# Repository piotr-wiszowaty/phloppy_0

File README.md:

phloppy\_0
=========

phloppy\_0 is a [Commodore Amiga](https://en.wikipedia.org/wiki/Amiga) floppy
drive emulator. It emulates four drives (`DF0:`, `DF1:`, `DF2:`, `DF3:`) and
is controlled through WiFi by an Android or a PC application.

`DF0:` - `DF3:` interoperation
--------------------------

The device is connected between the Amiga motherboard and the internal floppy
drive (DF0:). When a floppy image is inserted in the virtual DF0: the physical
drive input signals `SEL0` and `MTR0` are inactive. When there is no floppy image
in the virtual DF0: the `SEL0` and `MTR0` signals are passed from the Amiga
motherboard through the emulator to the physical drive.

When there are `DF1:` - `DF3`: physical drives connected to the Amiga, inserting
a floppy image in any of the virtual `DF1:` - `DF3:` will result in malfunction
of the drive.

Supported floppy image formats
------------------------------
 
Two floppy image formats are supported:
- ADF ([Amiga Disk File](https://en.wikipedia.org/wiki/Amiga\_Disk\_File)), 880 kB
- raw MFM - 12668 bytes per track, 160 tracks per disk

Hardware
--------

Main hardware components:
- STM32F446 - Cortex-M4 microcontroller; core of the emulator
- SDRAM, 8 MB; used for keeping floppy image contents
- ESP12-E - ESP8266 based WiFi module; provides WiFi hotspot to allow connection
  of a controlling application
- XC9272XL CPLD & two 8-channel open-drain buffers - interface between the
  microcontroller and the Amiga motherboard

On-board connectors:
- micro USB - for flashing the microcontroller
- SWD - for flashing/debugging the microcontroller
- JTAG - for flashing the CPLD
- UART (3.3 V) - for flashing the ESP8266
- power input - from the Amiga motherboard
- power output - to the physical floppy drive
- SEL2, SEL3 - input for the appropriate floppy selection signals
- male 34-pin pinheader - for connecting through a ribbon cable with
  the Amiga motherboard; for A600 the cable should be around 155 mm long
- female 34-pin pinheader - for connecting directly to the physical floppy
  drive

LEDs:
- green - indicates SDRAM active
- yellow - indicates read operation in progress
- red - indicates communication with the controlling application
  in progress
- blue - indicates write buffer is not empty (turn on the controlling
  application to write the buffer to the persistent memory)

In idle mode the device consumes around 170 mA. When the SDRAM is in active
mode the current consumption is around 185 mA.

Software
--------

Software components:
- `android/` - Android control application sources
- `cpld/` - CPLD design files
- `output/` - APK, JED, Gerbers, microcontroller firmware
- `pc/` - PC control application sources
- `uc/` - microcontroller firmware sources
- `wifi/` - ESP8266 source files

The Android application requires SDK level 15 and works at least on
Android 4.0.3 and 8.0.0.

The WiFi hotspot parameters are stored in the STM32 microcontroller and
read by ESP8266 during initialization. The parameters can be changed in source
code or after compilation in the microcontroller firmware image file.

License
-------

The project is licensed under GPL-3.0 license. See `LICENSE` for more information.
Parts of the project are covered by other licenses (see appropriate files for details):
- ESP8266 SPI driver by David Ogilvy (MetalPhreak)
- CMSIS header files by ARM LIMITED
- STM32 header files by STMicroelectronics

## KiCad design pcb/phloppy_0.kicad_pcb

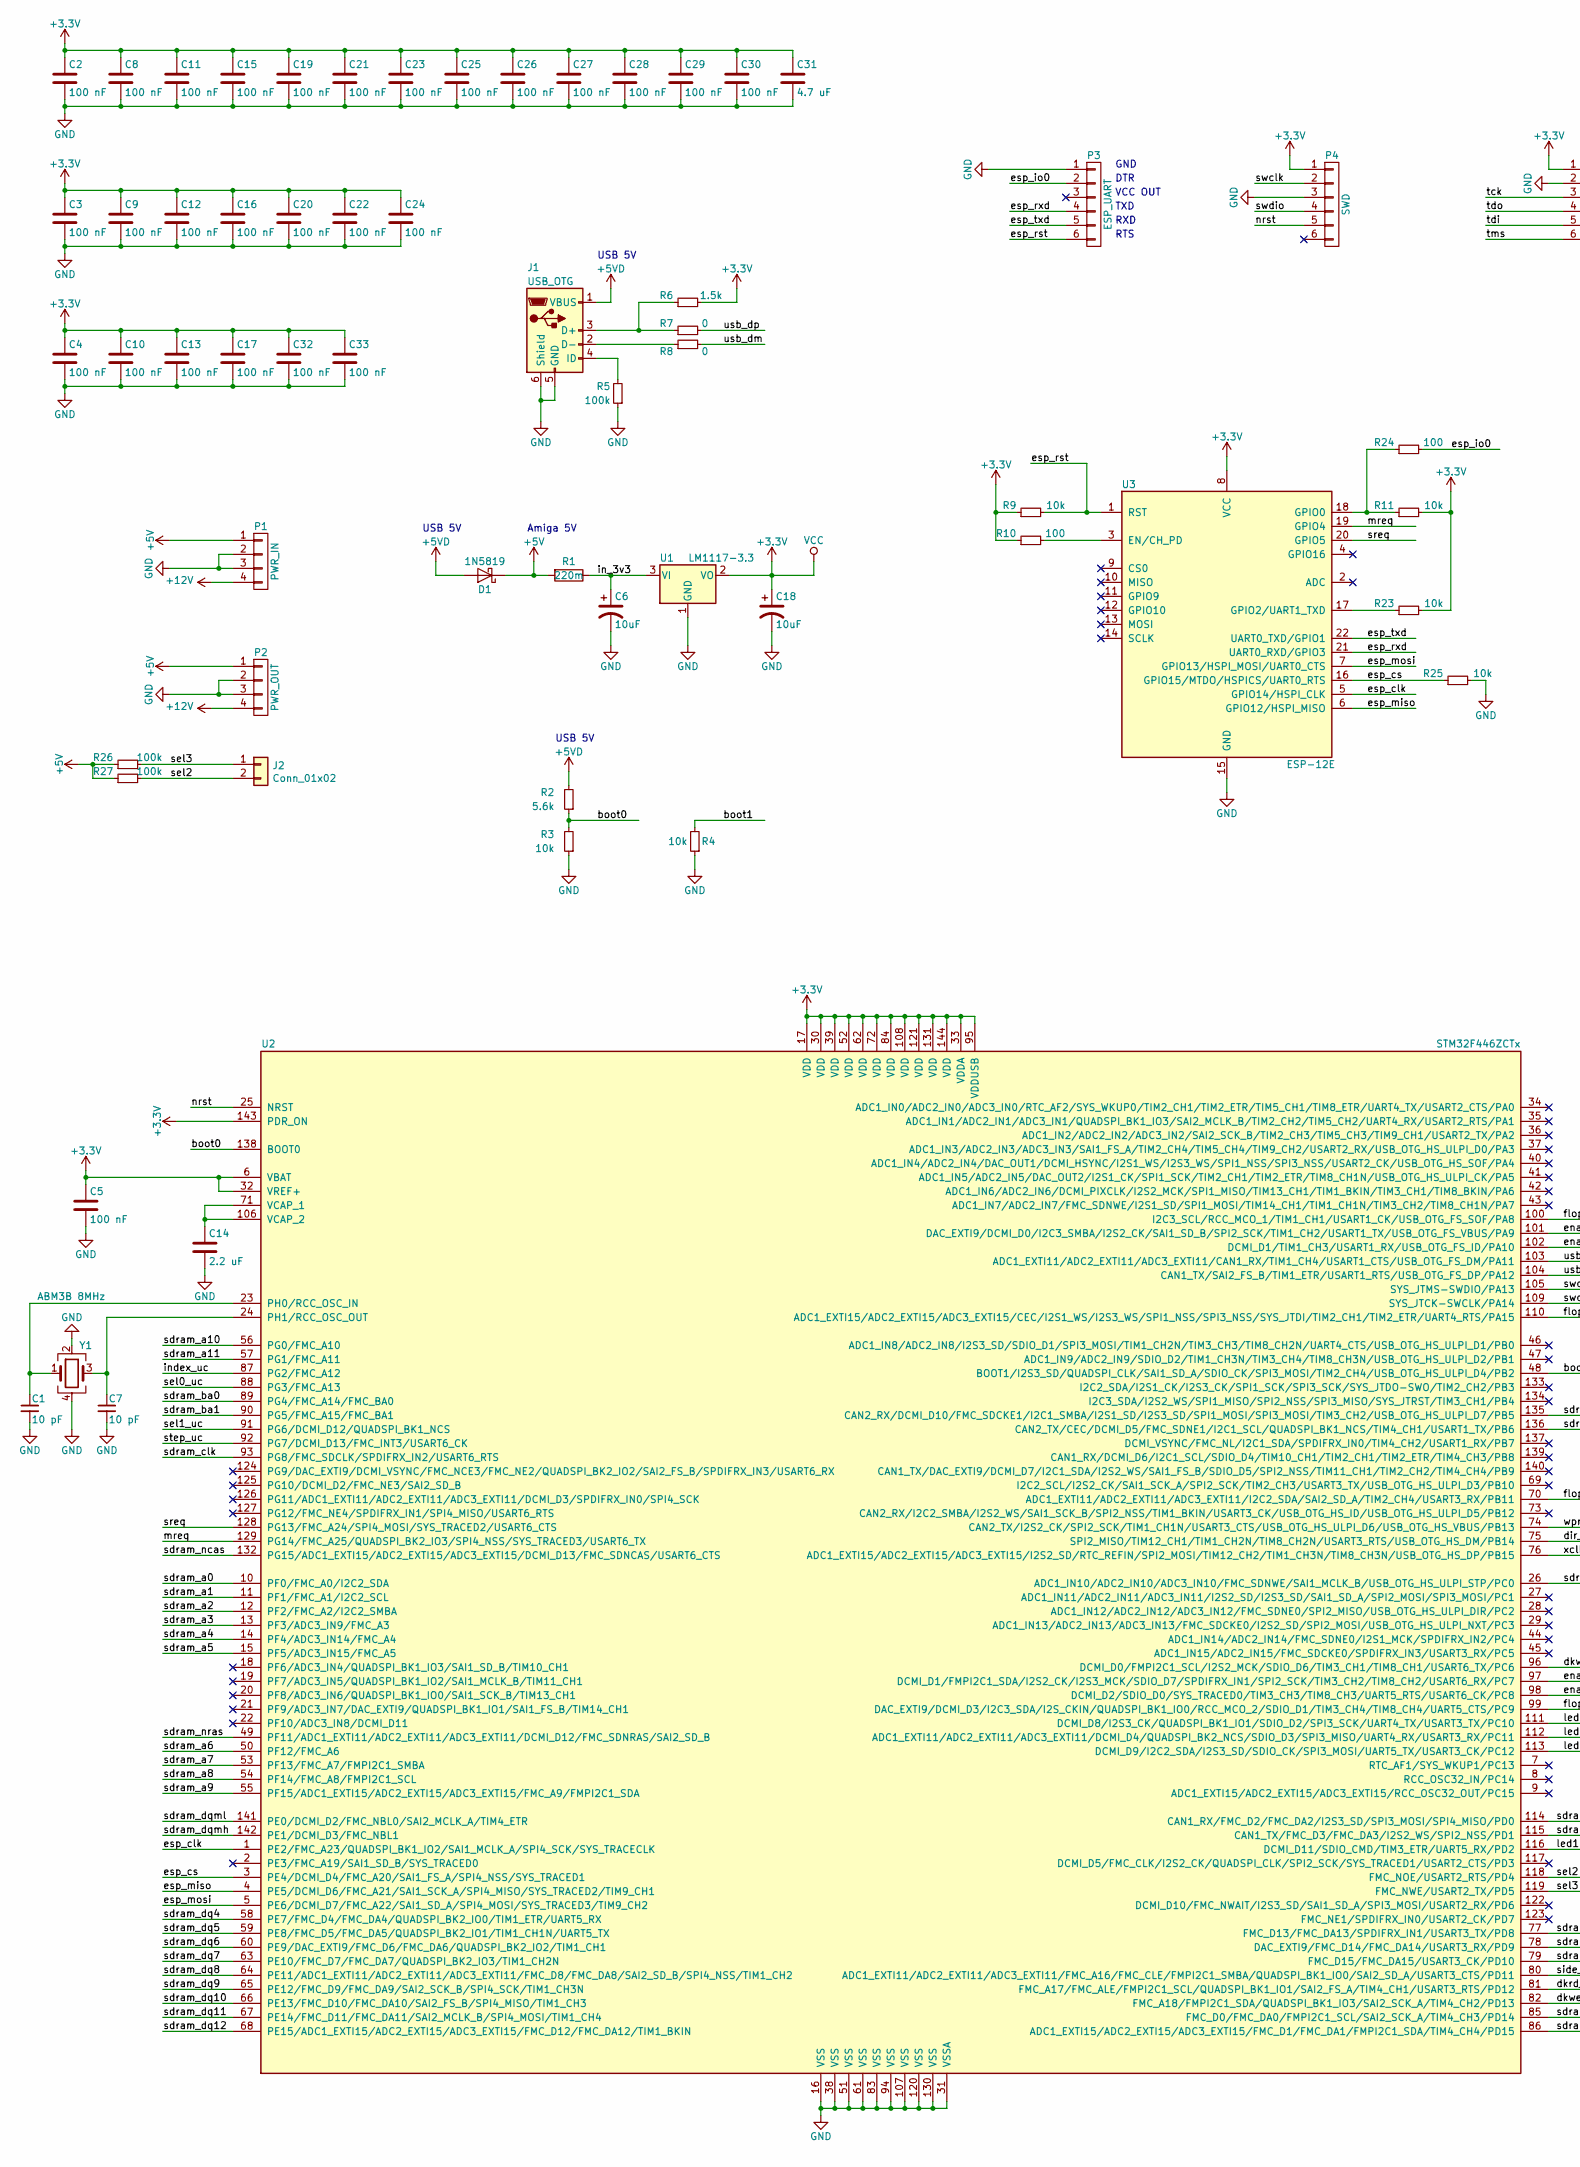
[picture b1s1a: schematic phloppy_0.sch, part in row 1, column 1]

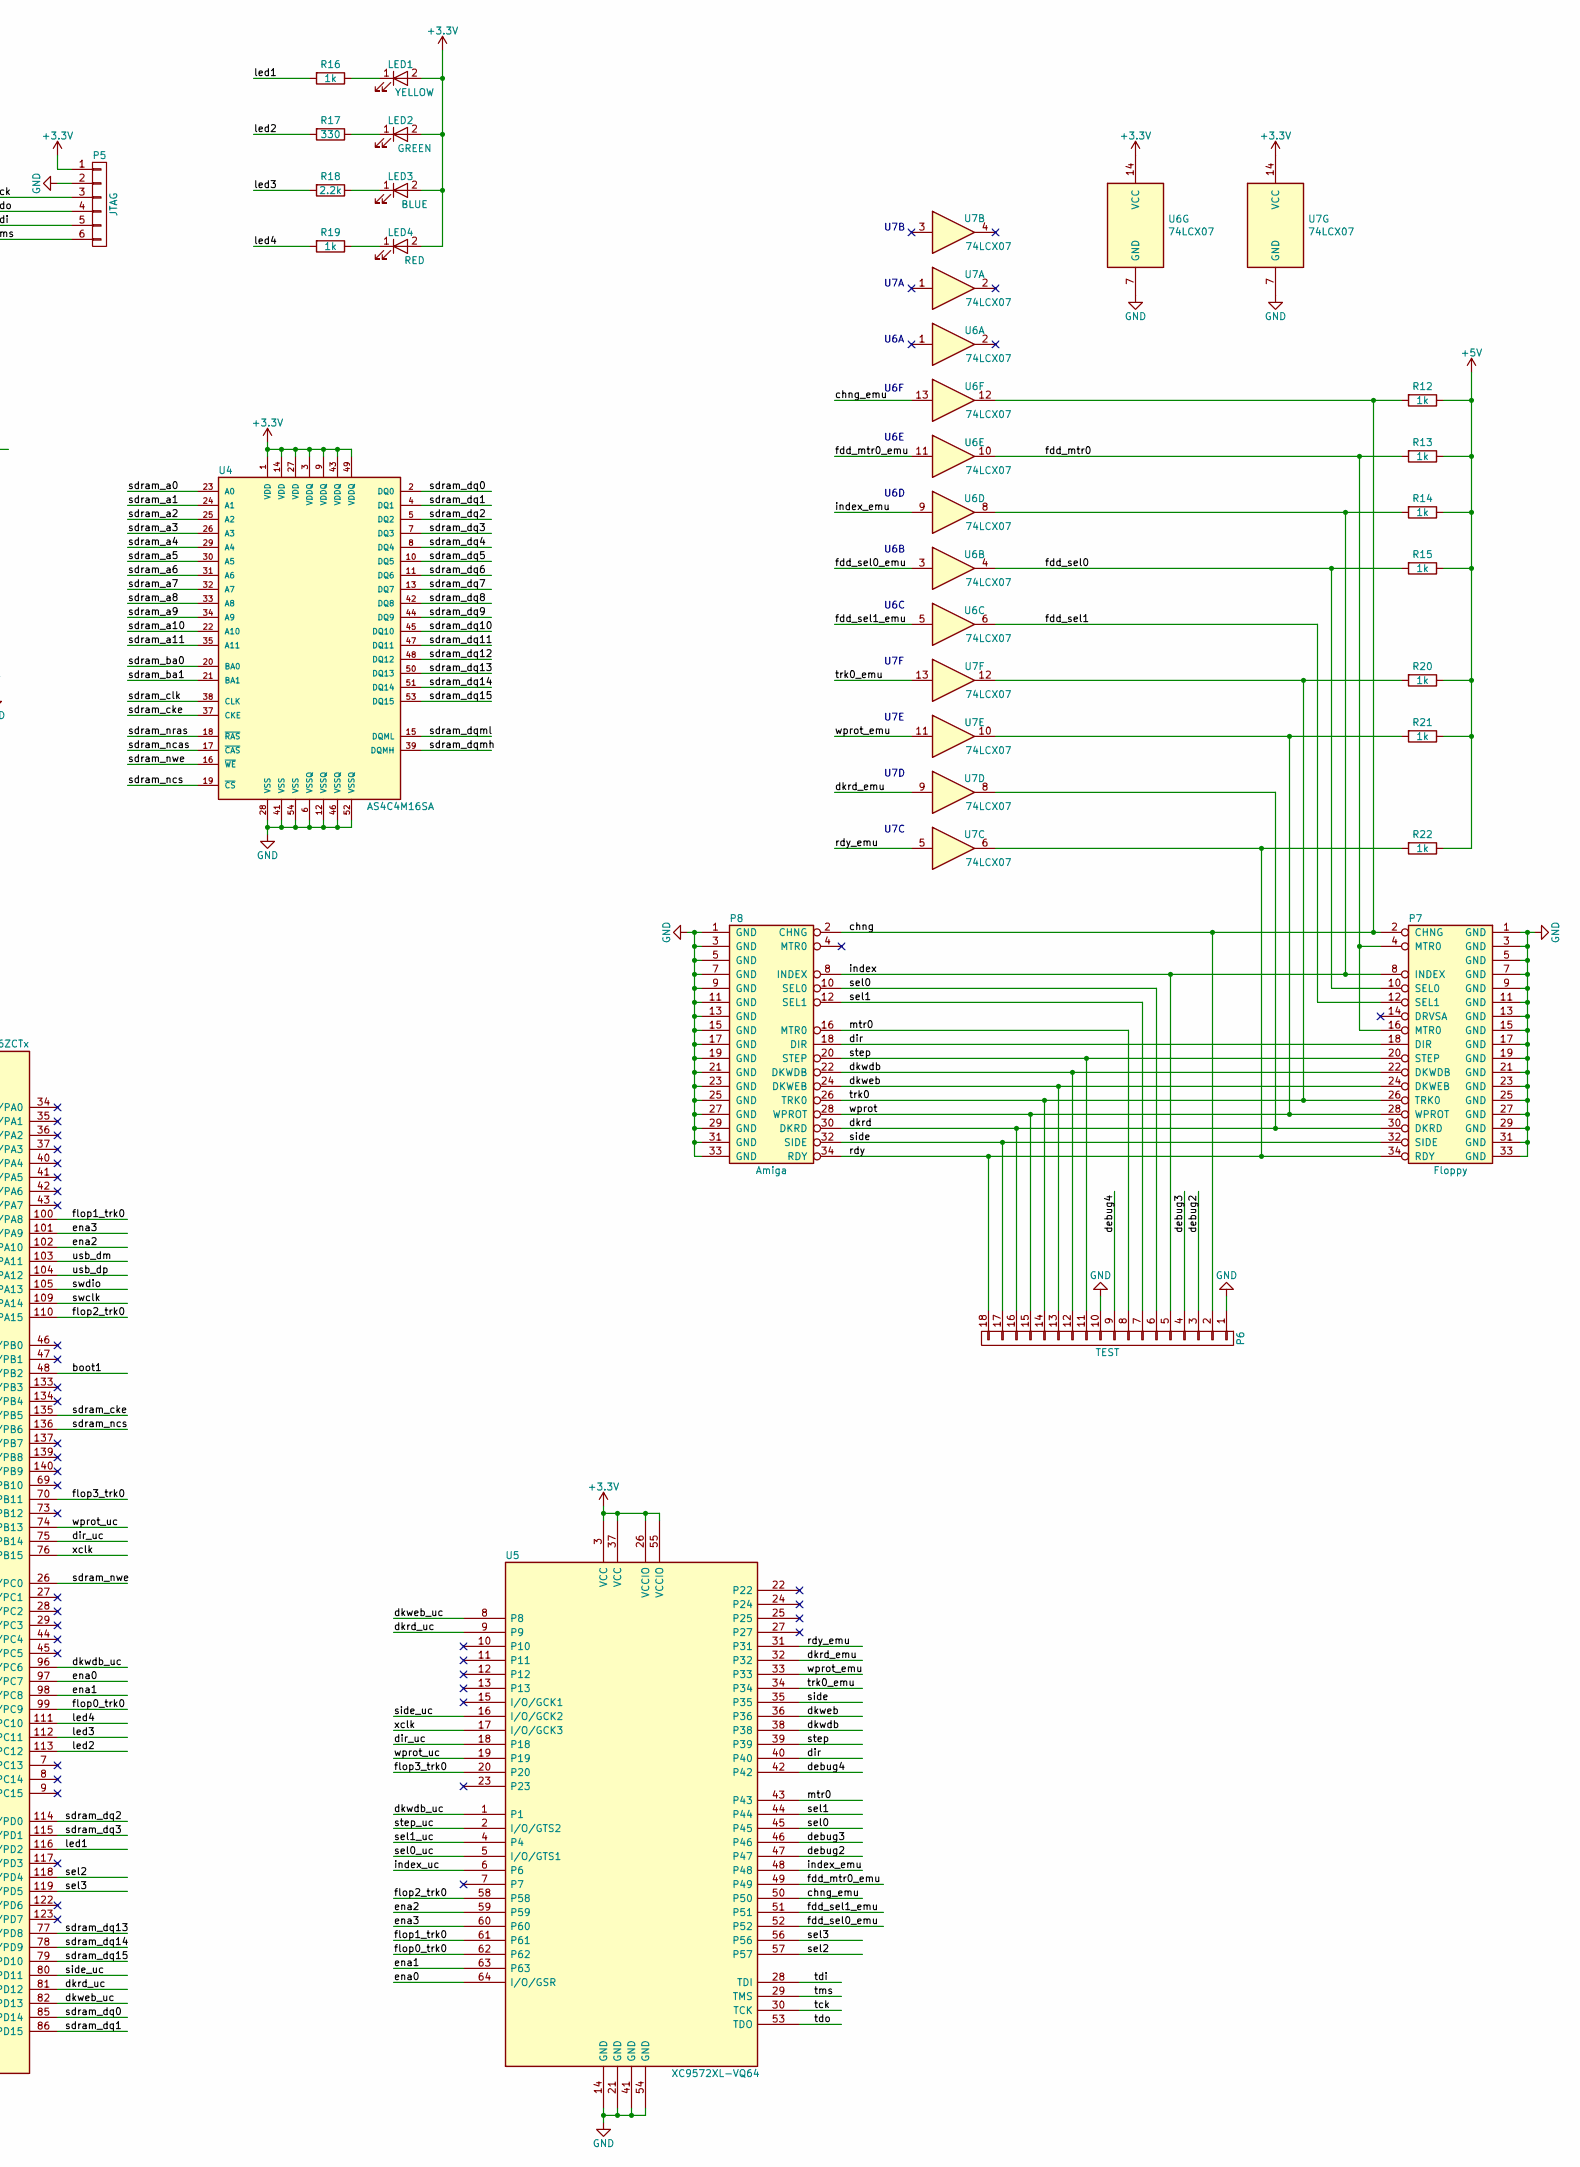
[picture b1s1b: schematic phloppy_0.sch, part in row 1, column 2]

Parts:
C1, C7: 10 pF; C_0805_HandSoldering
C2, C3, C4, C5, C8, C9, C10, C11, C12, C13, C15, C16, C17, C19, C20, C21, C22, C23, C24, C25, C26, C27, C28, C29, C30, C32, C33: 100 nF; C_0805_HandSoldering
C6: 10uF; CP_Tantalum_Case-B_EIA-3528-21_Hand
C14: 2.2 uF; C_1206_HandSoldering
C18: 10uF; Tantalum_Case-A_EIA-3216-18_Hand
C31: 4.7 uF; C_1206_HandSoldering
D1: 1N5819; D_SOD-123
J1: USB_OTG; USB_Micro-B_Molex_47346-0001
J2: Conn_01x02; Pin_Header_Angled_1x02_Pitch2.54mm
LED1: YELLOW; LED_0805_HandSoldering
LED2: GREEN; LED_0805_HandSoldering
LED3: BLUE; LED_0805_HandSoldering
LED4: RED; LED_0805_HandSoldering
P1: PWR_IN; Pin_Header_Angled_1x04_Pitch2.54mm
P2: PWR_OUT; Pin_Header_Angled_1x04_Pitch2.54mm
P3: ESP_UART; Pin_Header_Straight_1x06_Pitch2.54mm
P4: SWD; Pin_Header_Straight_1x06_Pitch2.54mm
P5: JTAG; Pin_Header_Straight_1x06_Pitch2.54mm
P6: TEST; Pin_Header_Straight_1x18_Pitch2.54mm
P7: Floppy; Pin_Header_Straight_2x17_Pitch2.54mm
P8: Amiga; Pin_Header_Straight_2x17_Pitch2.54mm
R1: 220m; R_1206_HandSoldering
R2: 5.6k; R_0805_HandSoldering
R3, R4, R9, R11, R23, R25: 10k; R_0805_HandSoldering
R5: 100k; R_0805_HandSoldering
R6: 1.5k; R_0805_HandSoldering
R7, R8: 0; R_0805_HandSoldering
R10, R24: 100; R_0805_HandSoldering
R12, R13, R14, R15, R16, R19, R20, R21, R22: 1k; R_0805_HandSoldering
R17: 330; R_0805_HandSoldering
R18: 2.2k; R_0805_HandSoldering
R26, R27: 100k; R_0805_2012Metric_Pad1.15x1.50mm_HandSolder
U1: LM1117-3.3; TO-252-2Lead
U2: STM32F446ZCTx; LQFP-144_20x20mm_Pitch0.5mm
U3: ESP-12E
U4: AS4C4M16SA; TSOP-II-54_22.22x10.16mm_Pitch0.8mm
U5: XC9572XL-VQ64; TQFP-64_10x10mm_Pitch0.5mm
U6, U7: 74LCX07; SOIC-14_3.9x8.7mm_Pitch1.27mm
Y1: ABM3B 8MHz; Crystal_SMD_Abracon_ABM3B-4pin_5.0x3.2mm

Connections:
+3V3: C2.1, C3.1, C4.1, C5.1, C8.1, C9.1, C10.1, C11.1, C12.1, C13.1, C15.1, C16.1, C17.1, C18.1, C19.1, C20.1, C21.1, C22.1, C23.1, C24.1, C25.1, C26.1, C27.1, C28.1, C29.1, C30.1, C31.1, C32.1, C33.1, LED1.2 (A), LED2.2 (A), LED3.2 (A), LED4.2 (A), P4.1, P5.1, R6.2, R9.1, R10.1, R11.2, R23.2, U1.2 (VO), U2.6 (VBAT), U2.17 (VDD), U2.30 (VDD), U2.32 (VREF+), U2.33 (VDDA), U2.39 (VDD), U2.52 (VDD), U2.62 (VDD), U2.72 (VDD), U2.84 (VDD), U2.95 (VDDUSB), U2.108 (VDD), U2.121 (VDD), U2.131 (VDD), U2.143 (PDR_ON), U2.144 (VDD), U3.8 (VCC), U4.1 (VDD), U4.3 (VDDQ), U4.9 (VDDQ), U4.14 (VDD), U4.27 (VDD), U4.43 (VDDQ), U4.49 (VDDQ), U5.3 (VCC), U5.26 (VCCIO), U5.37 (VCC), U5.55 (VCCIO), U6.14 (VCC), U7.14 (VCC)
+5V: D1.1 (K), P1.1, P2.1, R1.2, R12.1, R13.1, R14.1, R15.1, R20.1, R21.1, R22.1, R26.1, R27.1
+5VD: D1.2 (A), J1.1 (VBUS), R2.2
+12V: P1.4, P2.4
/boot0: R2.1, R3.2, U2.138 (BOOT0)
/boot1: R4.2, U2.48 (BOOT1/I2S3_SD/QUADSPI_CLK/SAI1_SD_A/SDI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)
/chng: P6.2, P7.2 (CHNG), P8.2 (CHNG), R12.2, U6.12
/chng_emu: U5.50, U6.13
/debug2: P6.3, U5.47
/debug3: P6.4, U5.46
/debug4: P6.9, U5.42
/dir: P7.18 (DIR), P8.18 (DIR), U5.40
/dir_uc: U2.75 (SPI2_MISO/TIM12_CH1/TIM1_CH2N/TIM8_CH2N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), U5.18
/dkrd: P6.16, P7.30 (DKRD), P8.30 (DKRD), U7.8
/dkrd_emu: U5.32, U7.9
/dkrd_uc: U2.81 (FMC_A17/FMC_ALE/FMPI2C1_SCL/QUADSPI_BK1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), U5.9
/dkwdb: P6.12, P7.22 (DKWDB), P8.22 (DKWDB), U5.38
/dkwdb_uc: U2.96 (DCMI_D0/FMPI2C1_SCL/I2S2_MCK/SDIO_D6/TI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), U5.1
/dkweb: P6.13, P7.24 (DKWEB), P8.24 (DKWEB), U5.36
/dkweb_uc: U2.82 (FMC_A18/FMPI2C1_SDA/QUADSPI_BK1_IO3/SAI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), U5.8
/ena0: U2.97 (DCMI_D1/FMPI2C1_SDA/I2S2_CK/I2S3_MCK/SD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), U5.64 (I/O/GSR)
/ena1: U2.98 (DCMI_D2/SDIO_D0/SYS_TRACED0/TIM3_CH3/TI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), U5.63
/ena2: U2.102 (DCMI_D1/TIM1_CH3/USART1_RX/USB_OTG_FS_I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), U5.59
/ena3: U2.101 (DAC_EXTI9/DCMI_D0/I2C3_SMBA/I2S2_CK/SAI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), U5.60
/esp_clk: U2.1 (PE2/FMC_A23/QUADSPI_BK1_IO2/SAI1_MCLK_A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), U3.5 (GPIO14/HSPI_CLK)
/esp_cs: R25.1, U2.3 (PE4/DCMI_D4/FMC_A20/SAI1_FS_A/SPI4_NSS/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), U3.16 (GPIO15/MTDO/HSPICS/UART0_RTS)
/esp_io0: P3.2, R24.2
/esp_miso: U2.4 (PE5/DCMI_D6/FMC_A21/SAI1_SCK_A/SPI4_MIS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), U3.6 (GPIO12/HSPI_MISO)
/esp_mosi: U2.5 (PE6/DCMI_D7/FMC_A22/SAI1_SD_A/SPI4_MOSI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), U3.7 (GPIO13/HSPI_MOSI/UART0_CTS)
/esp_rst: P3.6, R9.2, U3.1 (RST)
/esp_rxd: P3.4, U3.21 (UART0_RXD/GPIO3)
/esp_txd: P3.5, U3.22 (UART0_TXD/GPIO1)
/fdd_mtr0: P7.4 (MTR0), P7.16 (MTR0), R13.2, U6.10
/fdd_mtr0_emu: U5.49, U6.11
/fdd_sel0: P7.10 (SEL0), R15.2, U6.4
/fdd_sel0_emu: U5.52, U6.3
/fdd_sel1: P7.12 (SEL1), U6.6
/fdd_sel1_emu: U5.51, U6.5
/flop0_trk0: U2.99 (DAC_EXTI9/DCMI_D3/I2C3_SDA/I2S_CKIN/QUA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), U5.62
/flop1_trk0: U2.100 (I2C3_SCL/RCC_MCO_1/TIM1_CH1/USART1_CK/U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), U5.61
/flop2_trk0: U2.110 (ADC1_EXTI15/ADC2_EXTI15/ADC3_EXTI15/CEC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), U5.58
/flop3_trk0: U2.70 (ADC1_EXTI11/ADC2_EXTI11/ADC3_EXTI11/I2C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), U5.20
/in_3v3: C6.1, R1.1, U1.3 (VI)
/index: P6.5, P7.8 (INDEX), P8.8 (INDEX), R14.2, U6.8
/index_emu: U5.48, U6.9
/index_uc: U2.87 (PG2/FMC_A12), U5.6
/led1: R16.2, U2.116 (DCMI_D11/SDIO_CMD/TIM3_ETR/UART5_RX/PD2)
/led2: R17.2, U2.113 (DCMI_D9/I2C2_SDA/I2S3_SD/SDIO_CK/SPI3_M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)
/led3: R18.2, U2.112 (ADC1_EXTI11/ADC2_EXTI11/ADC3_EXTI11/DCM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)
/led4: R19.2, U2.111 (DCMI_D8/I2S3_CK/QUADSPI_BK1_IO1/SDIO_D2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)
/mreq: U2.129 (PG14/FMC_A25/QUADSPI_BK2_IO3/SPI4_NSS/S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), U3.19 (GPIO4)
/mtr0: P6.8, P8.16 (MTR0), U5.43
/nrst: P4.5, U2.25 (NRST)
/rdy: P6.18, P7.34 (RDY), P8.34 (RDY), R22.2, U7.6
/rdy_emu: U5.31, U7.5
/sdram_a0: U2.10 (PF0/FMC_A0/I2C2_SDA), U4.23 (A0)
/sdram_a1: U2.11 (PF1/FMC_A1/I2C2_SCL), U4.24 (A1)
/sdram_a2: U2.12 (PF2/FMC_A2/I2C2_SMBA), U4.25 (A2)
/sdram_a3: U2.13 (PF3/ADC3_IN9/FMC_A3), U4.26 (A3)
/sdram_a4: U2.14 (PF4/ADC3_IN14/FMC_A4), U4.29 (A4)
/sdram_a5: U2.15 (PF5/ADC3_IN15/FMC_A5), U4.30 (A5)
/sdram_a6: U2.50 (PF12/FMC_A6), U4.31 (A6)
/sdram_a7: U2.53 (PF13/FMC_A7/FMPI2C1_SMBA), U4.32 (A7)
/sdram_a8: U2.54 (PF14/FMC_A8/FMPI2C1_SCL), U4.33 (A8)
/sdram_a9: U2.55 (PF15/ADC1_EXTI15/ADC2_EXTI15/ADC3_EXTI1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), U4.34 (A9)
/sdram_a10: U2.56 (PG0/FMC_A10), U4.22 (A10)
/sdram_a11: U2.57 (PG1/FMC_A11), U4.35 (A11)
/sdram_ba0: U2.89 (PG4/FMC_A14/FMC_BA0), U4.20 (BA0)
/sdram_ba1: U2.90 (PG5/FMC_A15/FMC_BA1), U4.21 (BA1)
/sdram_cke: U2.135 (CAN2_RX/DCMI_D10/FMC_SDCKE1/I2C1_SMBA/I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), U4.37 (CKE)
/sdram_clk: U2.93 (PG8/FMC_SDCLK/SPDIFRX_IN2/USART6_RTS), U4.38 (CLK)
/sdram_dq0: U2.85 (FMC_D0/FMC_DA0/FMPI2C1_SCL/SAI2_SCK_A/T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), U4.2 (DQ0)
/sdram_dq1: U2.86 (ADC1_EXTI15/ADC2_EXTI15/ADC3_EXTI15/FMC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), U4.4 (DQ1)
/sdram_dq2: U2.114 (CAN1_RX/FMC_D2/FMC_DA2/I2S3_SD/SPI3_MOS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), U4.5 (DQ2)
/sdram_dq3: U2.115 (CAN1_TX/FMC_D3/FMC_DA3/I2S2_WS/SPI2_NSS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), U4.7 (DQ3)
/sdram_dq4: U2.58 (PE7/FMC_D4/FMC_DA4/QUADSPI_BK2_IO0/TIM1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), U4.8 (DQ4)
/sdram_dq5: U2.59 (PE8/FMC_D5/FMC_DA5/QUADSPI_BK2_IO1/TIM1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), U4.10 (DQ5)
/sdram_dq6: U2.60 (PE9/DAC_EXTI9/FMC_D6/FMC_DA6/QUADSPI_BK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), U4.11 (DQ6)
/sdram_dq7: U2.63 (PE10/FMC_D7/FMC_DA7/QUADSPI_BK2_IO3/TIM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), U4.13 (DQ7)
/sdram_dq8: U2.64 (PE11/ADC1_EXTI11/ADC2_EXTI11/ADC3_EXTI1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), U4.42 (DQ8)
/sdram_dq9: U2.65 (PE12/FMC_D9/FMC_DA9/SAI2_SCK_B/SPI4_SCK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), U4.44 (DQ9)
/sdram_dq10: U2.66 (PE13/FMC_D10/FMC_DA10/SAI2_FS_B/SPI4_MI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), U4.45 (DQ10)
/sdram_dq11: U2.67 (PE14/FMC_D11/FMC_DA11/SAI2_MCLK_B/SPI4_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), U4.47 (DQ11)
/sdram_dq12: U2.68 (PE15/ADC1_EXTI15/ADC2_EXTI15/ADC3_EXTI1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), U4.48 (DQ12)
/sdram_dq13: U2.77 (FMC_D13/FMC_DA13/SPDIFRX_IN1/USART3_TX/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), U4.50 (DQ13)
/sdram_dq14: U2.78 (DAC_EXTI9/FMC_D14/FMC_DA14/USART3_RX/PD9), U4.51 (DQ14)
/sdram_dq15: U2.79 (FMC_D15/FMC_DA15/USART3_CK/PD10), U4.53 (DQ15)
/sdram_dqmh: U2.142 (PE1/DCMI_D3/FMC_NBL1), U4.39 (DQMH)
/sdram_dqml: U2.141 (PE0/DCMI_D2/FMC_NBL0/SAI2_MCLK_A/TIM4_E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), U4.15 (DQML)
/sdram_ncas: U2.132 (PG15/ADC1_EXTI15/ADC2_EXTI15/ADC3_EXTI1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), U4.17 (~CAS~)
/sdram_ncs: U2.136 (CAN2_TX/CEC/DCMI_D5/FMC_SDNE1/I2C1_SCL/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), U4.19 (~CS~)
/sdram_nras: U2.49 (PF11/ADC1_EXTI11/ADC2_EXTI11/ADC3_EXTI1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), U4.18 (~RAS~)
/sdram_nwe: U2.26 (ADC1_IN10/ADC2_IN10/ADC3_IN10/FMC_SDNWE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), U4.16 (~WE~)
/sel0: P6.6, P8.10 (SEL0), U5.45
/sel0_uc: U2.88 (PG3/FMC_A13), U5.5 (I/O/GTS1)
/sel1: P6.7, P8.12 (SEL1), U5.44
/sel1_uc: U2.91 (PG6/DCMI_D12/QUADSPI_BK1_NCS), U5.4
/sel2: J2.2, R27.2, U2.118 (FMC_NOE/USART2_RTS/PD4), U5.57
/sel3: J2.1, R26.2, U2.119 (FMC_NWE/USART2_TX/PD5), U5.56
/side: P6.17, P7.32 (SIDE), P8.32 (SIDE), U5.35
/side_uc: U2.80 (ADC1_EXTI11/ADC2_EXTI11/ADC3_EXTI11/FMC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), U5.16 (I/O/GCK2)
/sreq: U2.128 (PG13/FMC_A24/SPI4_MOSI/SYS_TRACED2/USAR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), U3.20 (GPIO5)
/step: P6.11, P7.20 (STEP), P8.20 (STEP), U5.39
/step_uc: U2.92 (PG7/DCMI_D13/FMC_INT3/USART6_CK), U5.2 (I/O/GTS2)
/swclk: P4.2, U2.109 (SYS_JTCK-SWCLK/PA14)
/swdio: P4.4, U2.105 (SYS_JTMS-SWDIO/PA13)
/tck: P5.3, U5.30 (TCK)
/tdi: P5.5, U5.28 (TDI)
/tdo: P5.4, U5.53 (TDO)
/tms: P5.6, U5.29 (TMS)
/trk0: P6.14, P7.26 (TRK0), P8.26 (TRK0), R20.2, U7.12
/trk0_emu: U5.34, U7.13
/usb_dm: R8.2, U2.103 (ADC1_EXTI11/ADC2_EXTI11/ADC3_EXTI11/CAN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)
/usb_dp: R7.2, U2.104 (CAN1_TX/SAI2_FS_B/TIM1_ETR/USART1_RTS/U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)
/wprot: P6.15, P7.28 (WPROT), P8.28 (WPROT), R21.2, U7.10
/wprot_emu: U5.33, U7.11
/wprot_uc: U2.74 (CAN2_TX/I2S2_CK/SPI2_SCK/TIM1_CH1N/USAR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), U5.19
/xclk: U2.76 (ADC1_EXTI15/ADC2_EXTI15/ADC3_EXTI15/I2S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), U5.17 (I/O/GCK3)
GND: C1.2, C2.2, C3.2, C4.2, C5.2, C6.2, C7.2, C8.2, C9.2, C10.2, C11.2, C12.2, C13.2, C14.2, C15.2, C16.2, C17.2, C18.2, C19.2, C20.2, C21.2, C22.2, C23.2, C24.2, C25.2, C26.2, C27.2, C28.2, C29.2, C30.2, C31.2, C32.2, C33.2, J1.5 (GND), J1.6 (Shield), P1.2, P1.3, P2.2, P2.3, P3.1, P4.3, P5.2, P6.1, P6.10, P7.1 (GND), P7.3 (GND), P7.5 (GND), P7.7 (GND), P7.9 (GND), P7.11 (GND), P7.13 (GND), P7.15 (GND), P7.17 (GND), P7.19 (GND), P7.21 (GND), P7.23 (GND), P7.25 (GND), P7.27 (GND), P7.29 (GND), P7.31 (GND), P7.33 (GND), P8.1 (GND), P8.3 (GND), P8.5 (GND), P8.7 (GND), P8.9 (GND), P8.11 (GND), P8.13 (GND), P8.15 (GND), P8.17 (GND), P8.19 (GND), P8.21 (GND), P8.23 (GND), P8.25 (GND), P8.27 (GND), P8.29 (GND), P8.31 (GND), P8.33 (GND), R3.1, R4.1, R5.1, R25.2, U1.1 (GND), U2.16 (VSS), U2.31 (VSSA), U2.38 (VSS), U2.51 (VSS), U2.61 (VSS), U2.83 (VSS), U2.94 (VSS), U2.107 (VSS), U2.120 (VSS), U2.130 (VSS), U3.15 (GND), U4.6 (VSSQ), U4.12 (VSSQ), U4.28 (VSS), U4.41 (VSS), U4.46 (VSSQ), U4.52 (VSSQ), U4.54 (VSS), U5.14 (GND), U5.21 (GND), U5.41 (GND), U5.54 (GND), U6.7 (GND), U7.7 (GND), Y1.2, Y1.4
unnamed: C1.1, U2.23 (PH0/RCC_OSC_IN), Y1.1
unnamed: C7.1, U2.24 (PH1/RCC_OSC_OUT), Y1.3
unnamed: C14.1, U2.71 (VCAP_1), U2.106 (VCAP_2)
unnamed: J1.2 (D-), R8.1
unnamed: J1.3 (D+), R6.1, R7.1
unnamed: J1.4 (ID), R5.2
unnamed: LED1.1 (K), R16.1
unnamed: LED2.1 (K), R17.1
unnamed: LED3.1 (K), R18.1
unnamed: LED4.1 (K), R19.1
unnamed: R10.2, U3.3 (EN/CH_PD)
unnamed: R11.1, R24.1, U3.18 (GPIO0)
unnamed: R23.1, U3.17 (GPIO2/UART1_TXD)

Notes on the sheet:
USB 5V
Amiga 5V
DTR
VCC OUT
GND
TXD
RXD
RTS
U7B
U7A
U6A
U6F
U6E
U6D
U6B
U6C
U7F
U7E
U7D
U7C

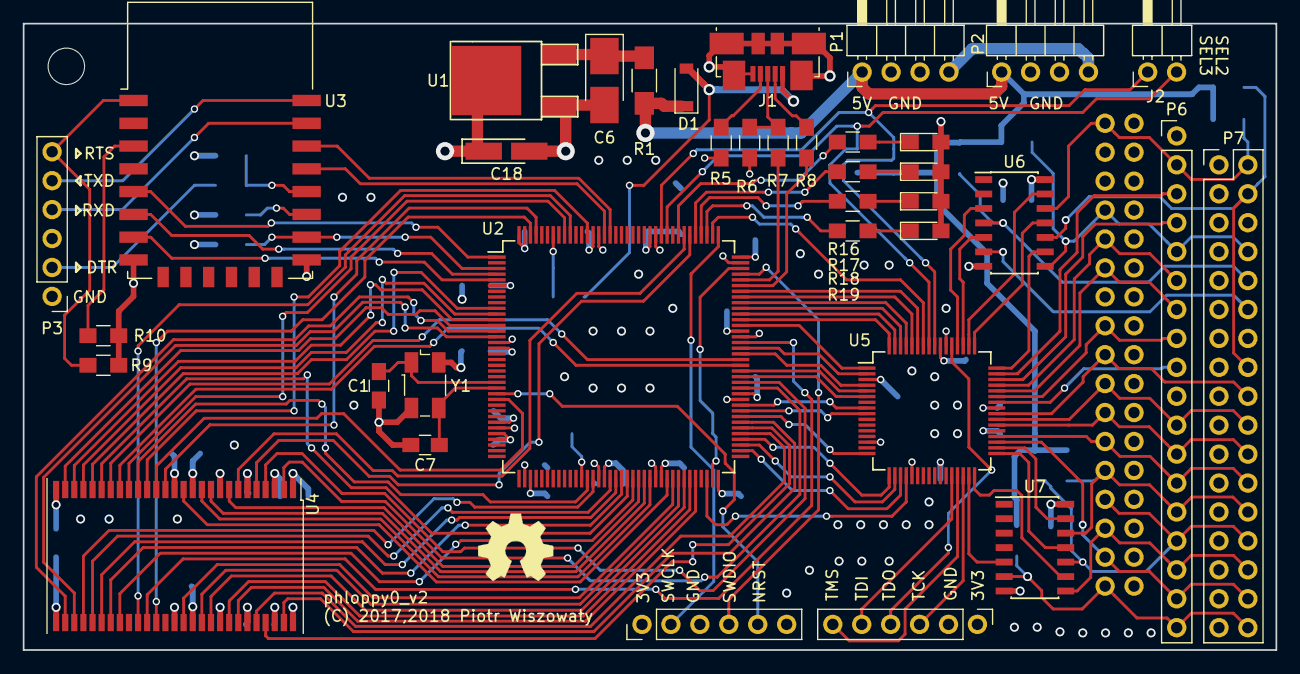
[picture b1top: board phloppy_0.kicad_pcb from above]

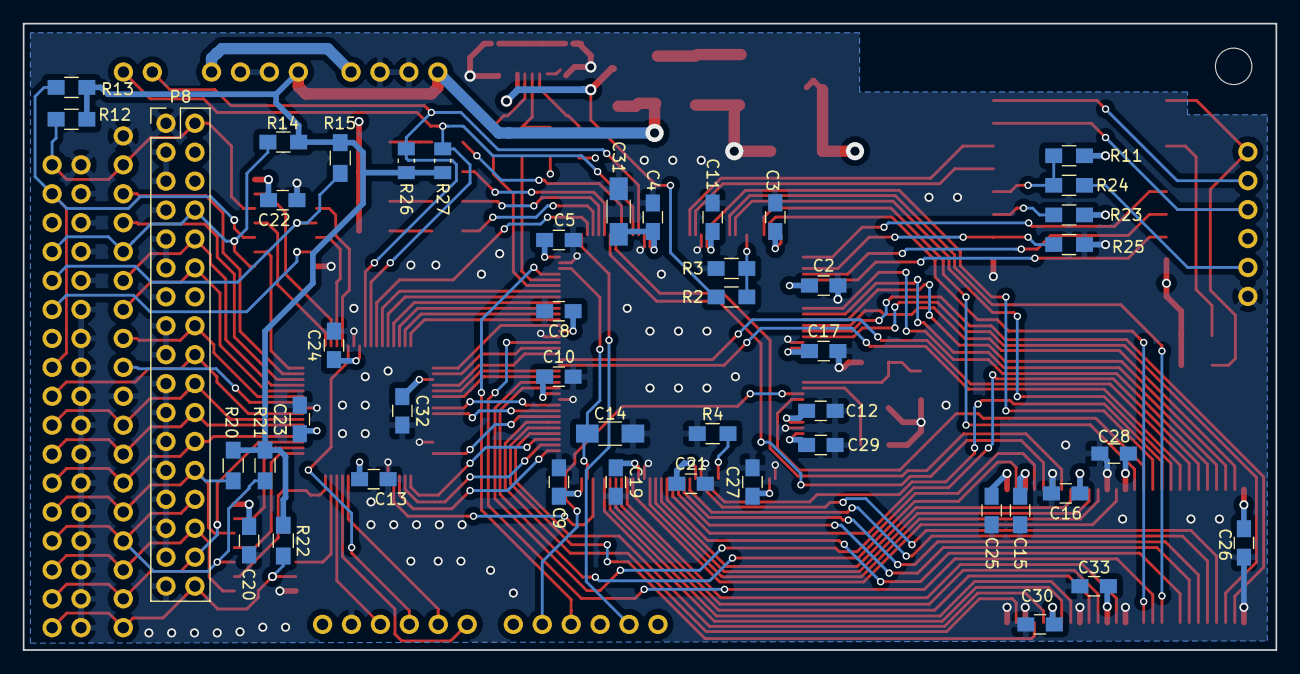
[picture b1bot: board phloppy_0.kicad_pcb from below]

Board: 4 copper layers, 110.0 x 55.0 mm, 83 parts (46 on the bottom side), 132 nets.

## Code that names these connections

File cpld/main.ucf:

net "dkweb_uc" loc = p8;
net "dkrd_uc" loc = p9;
net "side_uc" loc = p16;
net "xclk" loc = p17;
net "dir_uc" loc = p18;
net "wprot_uc" loc = p19;
net "dkwdb_uc" loc = p1;
net "step_uc" loc = p2;
net "sel1_uc" loc = p4;
net "sel0_uc" loc = p5;
net "index_uc" loc = p6;
net "flop2_trk0" loc = p58;
net "flop3_trk0" loc = p20;
net "ena2" loc = p59;
net "ena3" loc = p60;
net "flop1_trk0" loc = p61;
net "flop0_trk0" loc = p62;
net "ena1" loc = p63;
net "ena0" loc = p64;
net "rdy_emu" loc = p31;
net "dkrd_emu" loc = p32;
net "wprot_emu" loc = p33;
net "trk0_emu" loc = p34;
net "side" loc = p35;
net "dkweb" loc = p36;
net "dkwdb" loc = p38;
net "step" loc = p39;
net "dir" loc = p40;
net "debug4" loc = p42;
net "mtr0" loc = p43;
net "sel3" loc = p56;
net "sel2" loc = p57;
net "sel1" loc = p44;
net "sel0" loc = p45;
net "debug3" loc = p46;
net "debug2" loc = p47;
net "index_emu" loc = p48;
net "fdd_mtr0_emu" loc = p49;
net "chng_emu" loc = p50;
net "fdd_sel1_emu" loc = p51;
net "fdd_sel0_emu" loc = p52;

NET "xclk" BUFG = CLK;
NET "xclk" TNM_NET = xclk;
TIMESPEC TS_xclk = PERIOD "xclk" 10 MHz HIGH 50%;

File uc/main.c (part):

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	GPIO##port->OSPEEDR = (GPIO##port->OSPEEDR & ~(3<<2*(bit))) | ((speed) << 2*(bit));				\
	GPIO##port->AFR[(bit)>>3] = (GPIO##port->AFR[(bit)>>3] & ~(15<<4*((bit)&7))) | (altfun << 4*((bit) & 7))

#define FLOPPY0_SEL	(GPIOG->IDR & (1 << SEL0))
#define FLOPPY1_SEL	(GPIOG->IDR & (1 << SEL1))
#define FLOPPY2_SEL	(GPIOD->IDR & (1 << SEL2))
#define FLOPPY3_SEL	(GPIOD->IDR & (1 << SEL3))

#define EMPTY_TRACK_MASK_FLOPPY0_HEAD0	0x01
#define EMPTY_TRACK_MASK_FLOPPY0_HEAD1	0x02
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#define OP_SETUP_WIFI	0x80

// PA
#define FLOP1_TRK0	8
#define ENA3		9
#define ENA2		10
#define FLOP2_TRK0	15

// PB
#define SDCKE1		5
#define SDNE1		6
#define FLOP3_TRK0	11
#define WPROT		13
#define DIR		14
#define XCLK		15

// PC
#define SDNWE		0
#define DKWDB		6
#define ENA0		7
#define ENA1		8
#define FLOP0_TRK0	9
#define LED_RED		10
#define LED_BLUE	11
#define LED_GREEN	12
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#define SD_D2		0
#define SD_D3		1
#define LED_YELLOW	2
#define SEL2		4
#define SEL3		5
#define SD_D13		8
#define SD_D14		9
#define SD_D15		10
#define SIDE		11
#define DKRD		12
#define DKWEB		13
#define SD_D0		14
#define SD_D1		15

// PE
#define NBL0		0
#define NBL1		1
#define ESP_CLK		2
#define ESP_CS		4
#define ESP_MISO	5
#define ESP_MOSI	6
#define SD_D4		7
#define SD_D5		8
#define SD_D6		9
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// PG
#define SD_A10		0
#define SD_A11		1
#define INDEX		2
#define SEL0		3
#define BA0		4
#define BA1		5
#define SEL1		6
#define STEP		7
#define SDNCLK		8
#define SREQ		13
#define MREQ		14
#define SDNCAS		15

#if VERSION != 0
#define EXTI_SEL23_MSK	((1 << SEL2) | (1 << SEL3))
#else
#define EXTI_SEL23_MSK	0
#endif
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
void select_mfm_track()
{
	int head = (GPIOD->IDR & (1 << SIDE)) == 0;

	if (!FLOPPY0_SEL) {
		mfm_track = head ? mfm_track_floppy0_head1 : mfm_track_floppy0_head0;
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
inline void start_index_pulse()
{
	GPIOG->BSRR = 0x10000 << INDEX;
	TIM3->CNT = 0;
	TIM3->CR1 = TIM_CR1_CEN;
}

inline void stop_index_pulse()
{
	GPIOG->BSRR = 1 << INDEX;
	TIM3->CR1 = 0;
}

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	if (FLOPPY0_SEL) {					// rising edge
		stop_send_delay_timer();
		stop_sending_track_data();
		GPIOB->BSRR = 1 << WPROT;
		stop_index_pulse();
	} else {						// falling edge
		restart_send_delay_timer();
		mfm_track_type = (floppy_type & 0x01) != 0;
		if (floppy0_write_protected) {
			GPIOB->BSRR = 0x10000 << WPROT;
		}
	}
}
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	if (FLOPPY1_SEL) {					// rising edge
		stop_send_delay_timer();
		stop_sending_track_data();
		GPIOB->BSRR = 1 << WPROT;
		stop_index_pulse();
	} else {						// falling edge
		restart_send_delay_timer();
		mfm_track_type = (floppy_type & 0x02) != 0;
		if (floppy1_write_protected) {
			GPIOB->BSRR = 0x10000 << WPROT;
		}
	}
}

inline void exti_sel2()
{
	if (GPIOA->ODR & (1 << ENA2)) {
		if (FLOPPY2_SEL) {					// rising edge
			stop_send_delay_timer();
			stop_sending_track_data();
			GPIOB->BSRR = 1 << WPROT;
			stop_index_pulse();
		} else {						// falling edge
			restart_send_delay_timer();
			mfm_track_type = (floppy_type & 0x04) != 0;
			if (floppy2_write_protected) {
				GPIOB->BSRR = 0x10000 << WPROT;
			}
		}
	}
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
inline void exti_sel3()
{
	if (GPIOA->ODR & (1 << ENA3)) {
		if (FLOPPY3_SEL) {					// rising edge
			stop_send_delay_timer();
			stop_sending_track_data();
			GPIOB->BSRR = 1 << WPROT;
			stop_index_pulse();
		} else {						// falling edge
			restart_send_delay_timer();
			mfm_track_type = (floppy_type & 0x08) != 0;
			if (floppy3_write_protected) {
				GPIOB->BSRR = 0x10000 << WPROT;
			}
		}
	}
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				floppy0_current_cylinder++;
			}
		}
		GPIOC->BSRR = (floppy0_current_cylinder == 0 ? 0x10000 : 1) << FLOP0_TRK0;
	} else if (FLOPPY1_SEL == 0) {
		if (GPIOB->IDR & (1 << DIR)) {
			if (floppy1_current_cylinder) {
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				floppy1_current_cylinder++;
			}
		}
		GPIOA->BSRR = (floppy1_current_cylinder == 0 ? 0x10000 : 1) << FLOP1_TRK0;
	} else if (FLOPPY2_SEL == 0) {
		if (GPIOB->IDR & (1 << DIR)) {
			if (floppy2_current_cylinder) {
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				floppy2_current_cylinder++;
			}
		}
		GPIOA->BSRR = (floppy2_current_cylinder == 0 ? 0x10000 : 1) << FLOP2_TRK0;
	} else {
		if (GPIOB->IDR & (1 << DIR)) {
			if (floppy3_current_cylinder) {
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				floppy3_current_cylinder++;
			}
		}
		GPIOB->BSRR = (floppy3_current_cylinder == 0 ? 0x10000 : 1) << FLOP3_TRK0;
	}

	restart_send_delay_timer();
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
inline void exti_dkweb()
{
	int head = (GPIOD->IDR & (1 << SIDE)) == 0;
	int track_size;

	if (GPIOD->IDR & (1 << DKWEB)) {
		// rising edge
		if (FLOPPY0_SEL == 0) {
			if (floppy_type & 0x01) {
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	DMA2_Stream4->CR = (5 << DMA_SxCR_CHSEL_Pos) | DMA_SxCR_MINC | (1 << DMA_SxCR_DIR_Pos) | DMA_SxCR_EN;

	// Signal to master readiness for transmission
	GPIOG->BSRR = 1 << SREQ;

	// Wait for transmission end
	while (GPIOG->IDR & (1 << MREQ));
	GPIOG->BSRR = 0x10000 << SREQ;
}

unsigned int mfm_checksum(unsigned int *data, int length)
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	while ((RCC->CFGR & RCC_CFGR_SWS_Msk) != RCC_CFGR_SWS_PLL);

	// Setup ESP8266 communication pins
	setup_pin(G, SREQ, 1, 1, 0);
	setup_pin(E, ESP_CS, 2, 2, 5);
	setup_pin(E, ESP_CLK, 2, 2, 5);
	setup_pin(E, ESP_MISO, 2, 2, 5);
	setup_pin(E, ESP_MOSI, 2, 2, 5);

	// Setup floppy pins
	setup_pin(A, ENA3, 1, 1, 0);
	setup_pin(A, ENA2, 1, 1, 0);
	setup_pin(A, FLOP1_TRK0, 1, 1, 0);
	setup_pin(A, FLOP2_TRK0, 1, 1, 0);
	setup_pin(B, FLOP3_TRK0, 1, 1, 0);
	setup_pin(B, WPROT, 1, 1, 0);
	setup_pin(B, DIR, 0, 0, 0);
	setup_pin(C, ENA0, 1, 1, 0);
	setup_pin(C, ENA1, 1, 1, 0);
	setup_pin(C, FLOP0_TRK0, 1, 1, 0);
	setup_pin(D, SEL2, 0, 0, 0);
	setup_pin(D, SEL3, 0, 0, 0);
	setup_pin(D, SIDE, 0, 0, 0);
	setup_pin(D, DKWEB, 0, 0, 0);
	setup_pin(G, INDEX, 1, 2, 0);
	setup_pin(G, SEL0, 0, 0, 0);
	setup_pin(G, SEL1, 0, 0, 0);
	setup_pin(G, STEP, 0, 0, 0);

	GPIOB->BSRR = 1 << WPROT | 1 << FLOP3_TRK0;
	GPIOC->BSRR = 0x10000 << ENA0 | 0x10000 << ENA1 | 1 << FLOP0_TRK0;
	GPIOA->BSRR = 1 << FLOP1_TRK0 | 1 << FLOP2_TRK0 | 0x10000 << ENA2 | 0x10000 << ENA3;

	// Setup TIM12 - 10 MHz xclk
	RCC->APB1ENR |= RCC_APB1ENR_TIM12EN;
	setup_pin(B, XCLK, 2, 3, 9);					// TIM12_CH2
	TIM12->ARR = TIM_PCLK1 / TIM12_FREQ - 1;
	TIM12->CCR2 = (TIM_PCLK1 / TIM12_FREQ) / 2;
	TIM12->CCER = TIM_CCER_CC2E;
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
	// Setup TIM4 - MFM signal generator
	RCC->APB1ENR |= RCC_APB1ENR_TIM4EN;
	setup_pin(D, DKRD, 2, 2, 2);					// TIM4_CH1
	TIM4->PSC = TIM_PCLK1 / TIM4_FREQ - 1;
	TIM4->ARR = dkrd_tim_arr_lut[0];
	TIM4->CCR1 = 1;
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
	// Setup TIM8 - MFM signal scanner
	RCC->APB2ENR |= RCC_APB2ENR_TIM8EN;
	setup_pin(C, DKWDB, 2, 0, 3);					// TIM8_CH1
	TIM8->ARR = 0xffff;
	TIM8->PSC = TIM_PCLK2 / TIM8_FREQ - 1;
	TIM8->SMCR = (5 << TIM_SMCR_TS_Pos) | (4 << TIM_SMCR_SMS_Pos);
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
	// Setup EXTI interrupts (SEL0:G3, SEL1:G6, SEL2:D4, SEL3:D5, STEP:G7, SIDE:D11, DKWEB:D13)
	RCC->APB2ENR |= RCC_APB2ENR_SYSCFGEN;
	SYSCFG->EXTICR[0] = 0x6000;		// PG3
	SYSCFG->EXTICR[1] = 0x6633;		// PG7, PG6, PD5, PD4
	SYSCFG->EXTICR[2] = 0x3000;		// PD11
	SYSCFG->EXTICR[3] = 0x0030;		// PD13
	EXTI->IMR = (1 << SEL0) | (1 << SEL1) | (1 << STEP) | (1 << DKWEB) | (1 << SIDE) | EXTI_SEL23_MSK;
	EXTI->RTSR = (1 << SEL0) | (1 << SEL1) | (1 << STEP) | (1 << DKWEB) | (1 << SIDE) | EXTI_SEL23_MSK;
	EXTI->FTSR = (1 << SEL0) | (1 << SEL1) | (1 << DKWEB) | (1 << SIDE) | EXTI_SEL23_MSK;
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	GPIOC->BSRR = 0x10000 << LED_GREEN;

	for (;;) {
		if ((GPIOC->ODR & (1 << ENA0)) && (floppy0_encoded_cylinder != floppy0_current_cylinder)) {
			floppy0_encoded_cylinder = floppy0_current_cylinder;
			if (floppy_type & 0x01) {
				i = floppy0_current_cylinder * 2 * RAW_TRACK_SIZE;
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				encode_mfm_track(floppy0_data + i + ADF_TRACK_SIZE, mfm_track_floppy0_head1, floppy0_current_cylinder, 1, EMPTY_TRACK_MASK_FLOPPY0_HEAD1);
			}
		}
		if ((GPIOC->ODR & (1 << ENA1)) && (floppy1_encoded_cylinder != floppy1_current_cylinder)) {
			floppy1_encoded_cylinder = floppy1_current_cylinder;
			if (floppy_type & 0x02) {
				i = floppy1_current_cylinder * 2 * RAW_TRACK_SIZE;
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				encode_mfm_track(floppy1_data + i + ADF_TRACK_SIZE, mfm_track_floppy1_head1, floppy1_current_cylinder, 1, EMPTY_TRACK_MASK_FLOPPY1_HEAD1);
			}
		}
		if ((GPIOA->ODR & (1 << ENA2)) && (floppy2_encoded_cylinder != floppy2_current_cylinder)) {
			floppy2_encoded_cylinder = floppy2_current_cylinder;
			if (floppy_type & 0x04) {
				i = floppy2_current_cylinder * 2 * RAW_TRACK_SIZE;
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				encode_mfm_track(floppy2_data + i + ADF_TRACK_SIZE, mfm_track_floppy2_head1, floppy2_current_cylinder, 1, EMPTY_TRACK_MASK_FLOPPY2_HEAD1);
			}
		}
		if ((GPIOA->ODR & (1 << ENA3)) && (floppy3_encoded_cylinder != floppy3_current_cylinder)) {
			floppy3_encoded_cylinder = floppy3_current_cylinder;
			if (floppy_type & 0x08) {
				i = floppy3_current_cylinder * 2 * RAW_TRACK_SIZE;
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		}
		GPIOC->BSRR = ((tx_ptr != tx_end) ? 0x10000 : 1) << LED_BLUE;

		if ((GPIOG->IDR & (1 << MREQ))) {
			GPIOC->BSRR = 0x10000 << LED_RED;
			tx_pending = 0;
			esp_transaction(tx_buffer, rx_buffer);
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								floppy0_current_cylinder = 0;
								floppy0_encoded_cylinder = 0;
								floppy0_dirty_tt_ri = floppy0_dirty_tt_wi;
								GPIOC->BSRR = 0x10000 << FLOP0_TRK0;
								GPIOC->BSRR = 1 << ENA0;
								break;
							case OP_INSERT1:
								rx_state = NOP;
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								floppy1_current_cylinder = 0;
								floppy1_encoded_cylinder = 0;
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
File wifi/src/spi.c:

/*
* The MIT License (MIT)
* 
* Copyright (c) 2015 David Ogilvy (MetalPhreak)
* 
* Permission is hereby granted, free of charge, to any person obtaining a copy
* of this software and associated documentation files (the "Software"), to deal
* in the Software without restriction, including without limitation the rights
* to use, copy, modify, merge, publish, distribute, sublicense, and/or sell
* copies of the Software, and to permit persons to whom the Software is
* furnished to do so, subject to the following conditions:
* 
* The above copyright notice and this permission notice shall be included in all
* copies or substantial portions of the Software.
* 
* THE SOFTWARE IS PROVIDED "AS IS", WITHOUT WARRANTY OF ANY KIND, EXPRESS OR
* IMPLIED, INCLUDING BUT NOT LIMITED TO THE WARRANTIES OF MERCHANTABILITY,
* FITNESS FOR A PARTICULAR PURPOSE AND NONINFRINGEMENT. IN NO EVENT SHALL THE
* AUTHORS OR COPYRIGHT HOLDERS BE LIABLE FOR ANY CLAIM, DAMAGES OR OTHER
* LIABILITY, WHETHER IN AN ACTION OF CONTRACT, TORT OR OTHERWISE, ARISING FROM,
* OUT OF OR IN CONNECTION WITH THE SOFTWARE OR THE USE OR OTHER DEALINGS IN THE
* SOFTWARE.
*
* Changes from the original:
* - move initialization code directly into spi_init
* - simplify spi_transaction
* - reformat (to closer match the rest of the project)
*/

#include <eagle_soc.h>
#include "spi.h"

void spi_init()
{
	WRITE_PERI_REG(PERIPHS_IO_MUX, 0x105);
	PIN_FUNC_SELECT(PERIPHS_IO_MUX_MTDI_U, 2); //GPIO12 is HSPI MISO pin (Master Data In)
	PIN_FUNC_SELECT(PERIPHS_IO_MUX_MTCK_U, 2); //GPIO13 is HSPI MOSI pin (Master Data Out)
	PIN_FUNC_SELECT(PERIPHS_IO_MUX_MTMS_U, 2); //GPIO14 is HSPI CLK pin (Clock)
	PIN_FUNC_SELECT(PERIPHS_IO_MUX_MTDO_U, 2); //GPIO15 is HSPI CS pin (Chip Select / Slave Select)

#if 0
	// 1 MHz
	WRITE_PERI_REG(SPI_CLOCK(HSPI), 7 << SPI_CLKDIV_PRE_S | 9 << SPI_CLKCNT_N_S | 5 << SPI_CLKCNT_H_S);
#else
	// 10 MHz
	WRITE_PERI_REG(SPI_CLOCK(HSPI), 7 << SPI_CLKCNT_N_S | 3 << SPI_CLKCNT_H_S);
#endif

	spi_tx_byte_order(SPI_BYTE_ORDER_LOW_TO_HIGH);
	spi_rx_byte_order(SPI_BYTE_ORDER_LOW_TO_HIGH); 

	SET_PERI_REG_MASK(SPI_USER(HSPI), SPI_CS_SETUP|SPI_CS_HOLD);
	CLEAR_PERI_REG_MASK(SPI_USER(HSPI), SPI_FLASH_MODE);
}

// Description: Configures SPI mode parameters for clock edge and clock polarity.
//  Parameters: spi_cpha - (0) Data is valid on clock leading edge
//			             (1) Data is valid on clock trailing edge
//			  spi_cpol - (0) Clock is low when inactive
//			             (1) Clock is high when inactive

void spi_mode(uint8 spi_cpha, uint8 spi_cpol)
{
	if (!spi_cpha == !spi_cpol) {
		CLEAR_PERI_REG_MASK(SPI_USER(HSPI), SPI_CK_OUT_EDGE);
	} else {
		SET_PERI_REG_MASK(SPI_USER(HSPI), SPI_CK_OUT_EDGE);
	}
	if (spi_cpol) {
		SET_PERI_REG_MASK(SPI_PIN(HSPI), SPI_IDLE_EDGE);
	} else {
		CLEAR_PERI_REG_MASK(SPI_PIN(HSPI), SPI_IDLE_EDGE);
	}
}

// Description: Setup the byte order for shifting data out of buffer
//  Parameters: byte_order - SPI_BYTE_ORDER_HIGH_TO_LOW (1) 
//						   Data is sent out starting with Bit31 and down to Bit0
//
//						   SPI_BYTE_ORDER_LOW_TO_HIGH (0)
//						   Data is sent out starting with the lowest BYTE, from 
//						   MSB to LSB, followed by the second lowest BYTE, from
//						   MSB to LSB, followed by the second highest BYTE, from
//						   MSB to LSB, followed by the highest BYTE, from MSB to LSB
//						   0xABCDEFGH would be sent as 0xGHEFCDAB

void spi_tx_byte_order(uint8 byte_order)
{
	if (byte_order) {
		SET_PERI_REG_MASK(SPI_USER(HSPI), SPI_WR_BYTE_ORDER);
	} else {
		CLEAR_PERI_REG_MASK(SPI_USER(HSPI), SPI_WR_BYTE_ORDER);
	}
}

// Description: Setup the byte order for shifting data into buffer
//  Parameters: byte_order - SPI_BYTE_ORDER_HIGH_TO_LOW (1) 
//						   Data is read in starting with Bit31 and down to Bit0
//
//						   SPI_BYTE_ORDER_LOW_TO_HIGH (0)
//						   Data is read in starting with the lowest BYTE, from 
//						   MSB to LSB, followed by the second lowest BYTE, from
//						   MSB to LSB, followed by the second highest BYTE, from
//						   MSB to LSB, followed by the highest BYTE, from MSB to LSB
//						   0xABCDEFGH would be read as 0xGHEFCDAB

void spi_rx_byte_order(uint8 byte_order)
{
	if (byte_order) {
		SET_PERI_REG_MASK(SPI_USER(HSPI), SPI_RD_BYTE_ORDER);
	} else {
		CLEAR_PERI_REG_MASK(SPI_USER(HSPI), SPI_RD_BYTE_ORDER);
	}
}

// Description: SPI transaction function
//  Parameters: data - buffer
//			    length - buffer length

void spi_transaction(uint8 *data, int32 length)
{
	uint32 *p;
	int i;
	uint16 l = (length << 3) - 1;

	while (spi_busy(HSPI));

	CLEAR_PERI_REG_MASK(SPI_USER(HSPI), SPI_USR_MOSI | SPI_USR_MISO | SPI_USR_COMMAND | SPI_USR_ADDR | SPI_USR_DUMMY | SPI_DOUTDIN);
	SET_PERI_REG_MASK(SPI_USER(HSPI), SPI_USR_MOSI | SPI_DOUTDIN);
	WRITE_PERI_REG(SPI_USER1(HSPI), (l << SPI_USR_MOSI_BITLEN_S) | ((-l & 0xffff) << SPI_USR_MISO_BITLEN_S));
	for (i = 0, p = (uint32 *) data; i < length; i += 4) {
		WRITE_PERI_REG(SPI_W0(HSPI) + i, *p++);
	}

	SET_PERI_REG_MASK(SPI_CMD(HSPI), SPI_USR);
	while (spi_busy(HSPI));

	for (i = 0, p = (uint32 *) data; i < length; i += 4) {
		*p++ = READ_PERI_REG(SPI_W0(HSPI) + i);
	}
}

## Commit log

2018-08-17 Add sources
2018-08-17 uc: Compile version 2 by defualt
2018-08-17 android: Update gitignore
2018-08-17 pcb: Update gitignore
2018-08-17 pcb: Add OSHW symbol
2018-08-17 Add compilation output and Gerber files
2018-08-18 Add photos of the device

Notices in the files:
uc/main.c:
Copyright (C) 2016-2018 Piotr Wiszowaty
This program is free software: you can redistribute it and/or modify
it under the terms of the GNU General Public License as published by
the Free Software Foundation, either version 3 of the License, or
(at your option) any later version.
pcb/phloppy_0.kicad_pcb:
(C) 2017,2018 Piotr Wiszowaty
